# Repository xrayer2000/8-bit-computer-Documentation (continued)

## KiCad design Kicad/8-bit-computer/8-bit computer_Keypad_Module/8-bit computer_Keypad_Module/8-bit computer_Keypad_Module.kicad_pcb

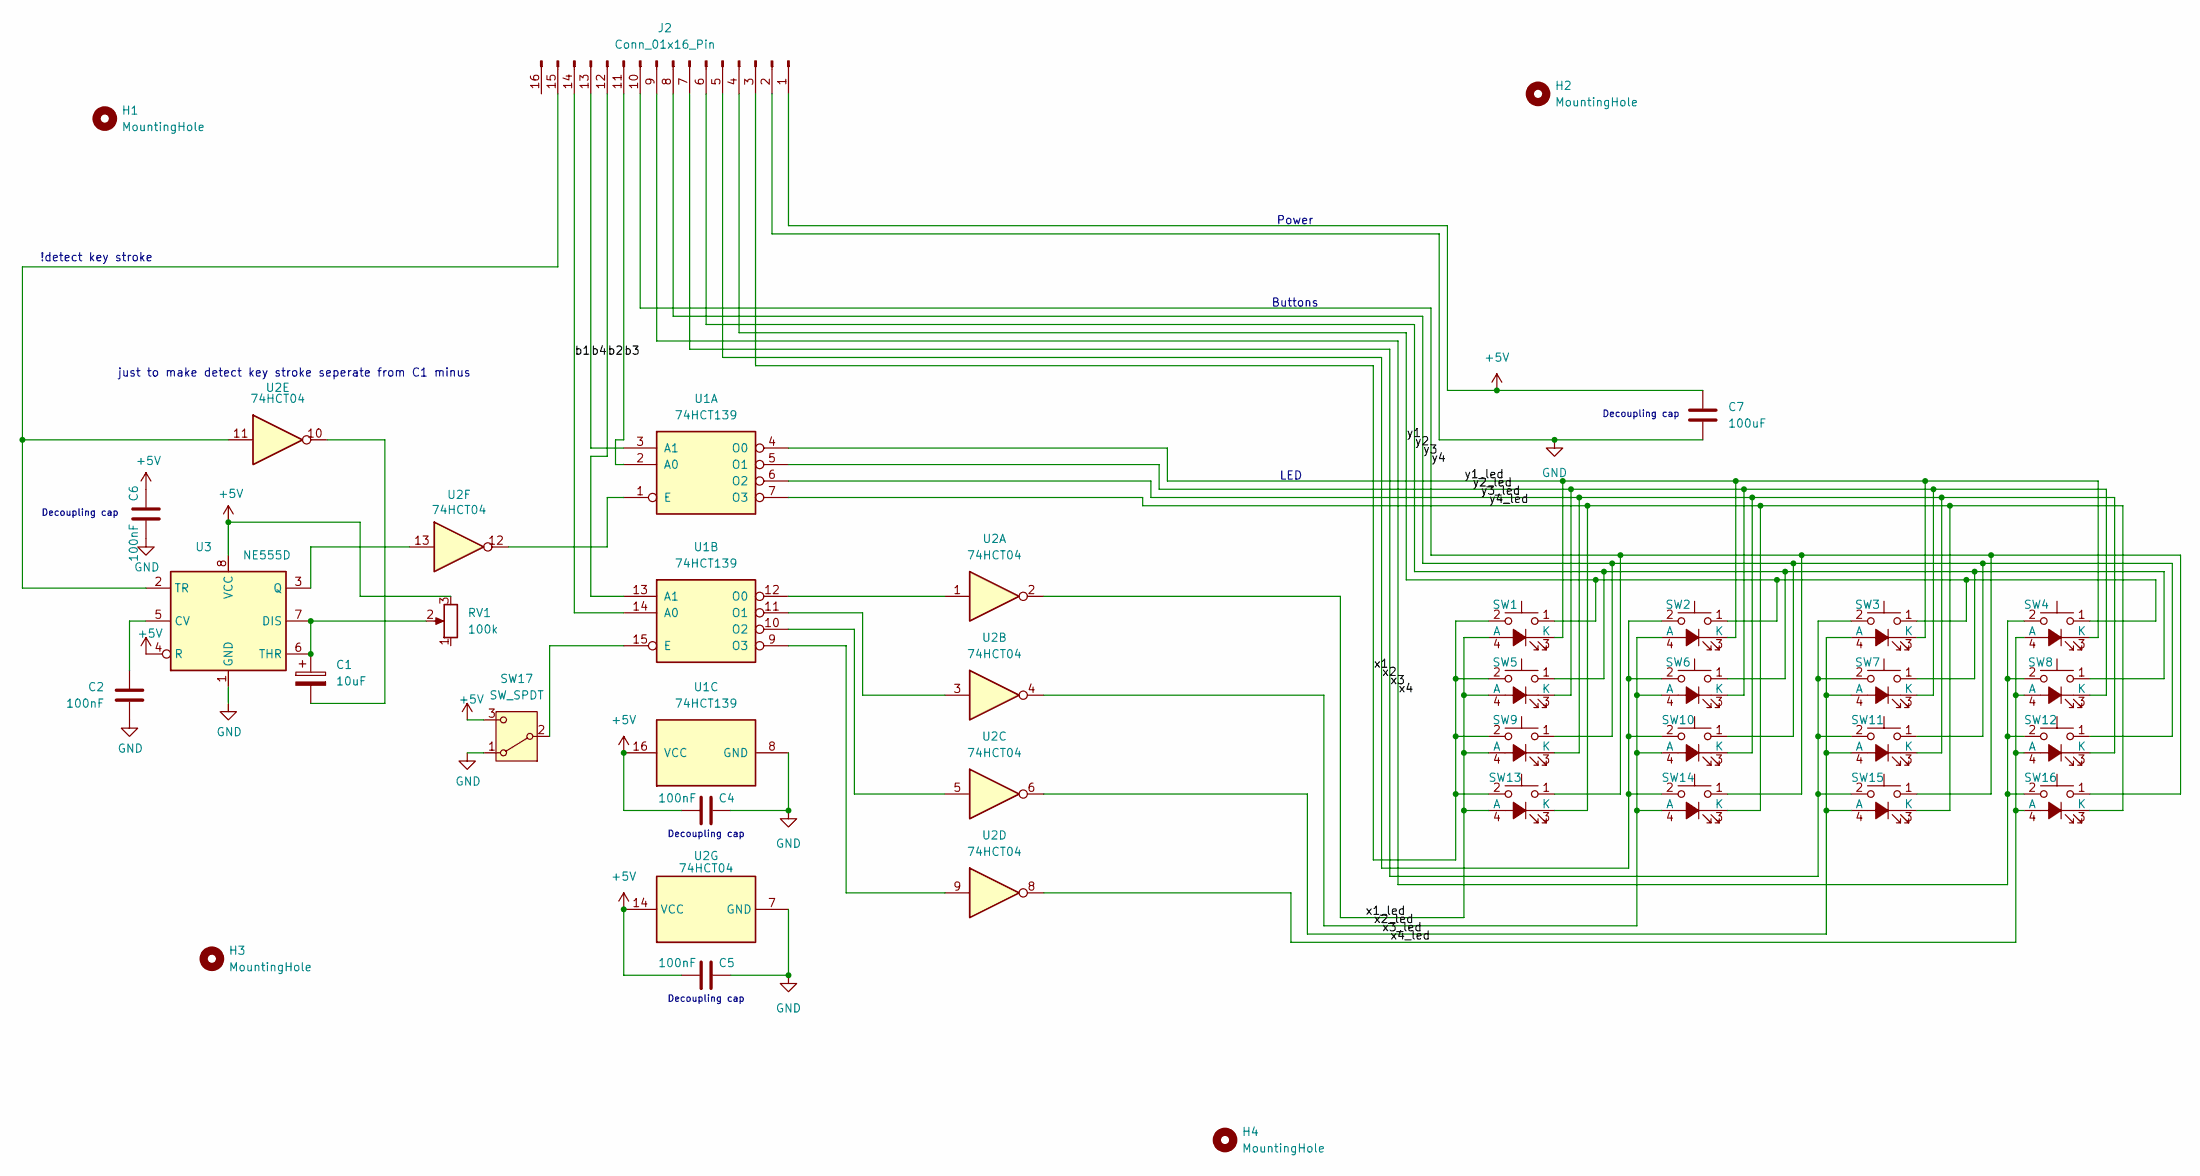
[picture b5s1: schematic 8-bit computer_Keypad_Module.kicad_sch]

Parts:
C1: 10uF; CP_Radial_D5.0mm_P2.00mm
C2: 100nF; CP_Radial_D5.0mm_P2.00mm
C4, C5, C6: 100nF; C_Disc_D3.0mm_W1.6mm_P2.50mm
C7: 100uF; CP_Radial_D4.0mm_P1.50mm
H1, H2, H3, H4: MountingHole; MountingHole_3.2mm_M3_DIN965_Pad
J2: Conn_01x16_Pin; IDC-Header_2x08_P2.54mm_Vertical
RV1: 100k; Potentiometer_Bourns_3296W_Vertical
SW1, SW2, SW3, SW4, SW5, SW6, SW7, SW8, SW9, SW10, SW11, SW12, SW13, SW14, SW15, SW16: CherryMX_LED; CherryMX_1.00u_LED
SW17: SW_SPDT; hole for bistable switch
U1: 74HCT139; DIP-16_W7.62mm
U2: 74HCT04; DIP-14_W7.62mm
U3: NE555D; DIP-8_W7.62mm

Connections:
+5V: C4.1, C5.1, C6.2, C7.2, J2.1, RV1.3, SW17.3 (C), U1.16 (VCC), U2.14 (VCC), U3.4 (R), U3.8 (VCC)
/b1: J2.14, U1.14 (A0)
/b2: J2.12, U1.13 (A1)
/b3: J2.11, U1.2 (A0)
/b4: J2.13, U1.3 (A1)
/x1: J2.3, SW1.2, SW5.2, SW9.2, SW13.2
/x1_led: SW1.4 (A), SW5.4 (A), SW9.4 (A), SW13.4 (A), U2.2
/x2: J2.5, SW2.2, SW6.2, SW10.2, SW14.2
/x2_led: SW2.4 (A), SW6.4 (A), SW10.4 (A), SW14.4 (A), U2.4
/x3: J2.7, SW3.2, SW7.2, SW11.2, SW15.2
/x3_led: SW3.4 (A), SW7.4 (A), SW11.4 (A), SW15.4 (A), U2.6
/x4: J2.9, SW4.2, SW8.2, SW12.2, SW16.2
/x4_led: SW4.4 (A), SW8.4 (A), SW12.4 (A), SW16.4 (A), U2.8
/y1: J2.4, SW1.1, SW2.1, SW3.1, SW4.1
/y1_led: SW1.3 (K), SW2.3 (K), SW3.3 (K), SW4.3 (K), U1.4 (O0)
/y2: J2.6, SW5.1, SW6.1, SW7.1, SW8.1
/y2_led: SW5.3 (K), SW6.3 (K), SW7.3 (K), SW8.3 (K), U1.5 (O1)
/y3: J2.8, SW9.1, SW10.1, SW11.1, SW12.1
/y3_led: SW9.3 (K), SW10.3 (K), SW11.3 (K), SW12.3 (K), U1.6 (O2)
/y4: J2.10, SW13.1, SW14.1, SW15.1, SW16.1
/y4_led: SW13.3 (K), SW14.3 (K), SW15.3 (K), SW16.3 (K), U1.7 (O3)
GND: C2.1, C4.2, C5.2, C6.1, C7.1, J2.2, SW17.1 (A), U1.8 (GND), U2.7 (GND), U3.1 (GND)
unnamed: C1.2, U2.10
unnamed: J2.15, U2.11, U3.2 (TR)
unnamed: SW17.2 (B), U1.15 (E)
unnamed: U1.1 (E), U2.12
unnamed: U1.12 (O0), U2.1
unnamed: U1.11 (O1), U2.3
unnamed: U1.10 (O2), U2.5
unnamed: U1.9 (O3), U2.9
unnamed: C2.2, U3.5 (CV)
unnamed: C1.1, RV1.2, U3.6 (THR), U3.7 (DIS)
unnamed: U2.13, U3.3 (Q)

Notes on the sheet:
Decoupling cap
Power
Buttons
just to make detect key stroke seperate from C1 minus
!detect key stroke
LED

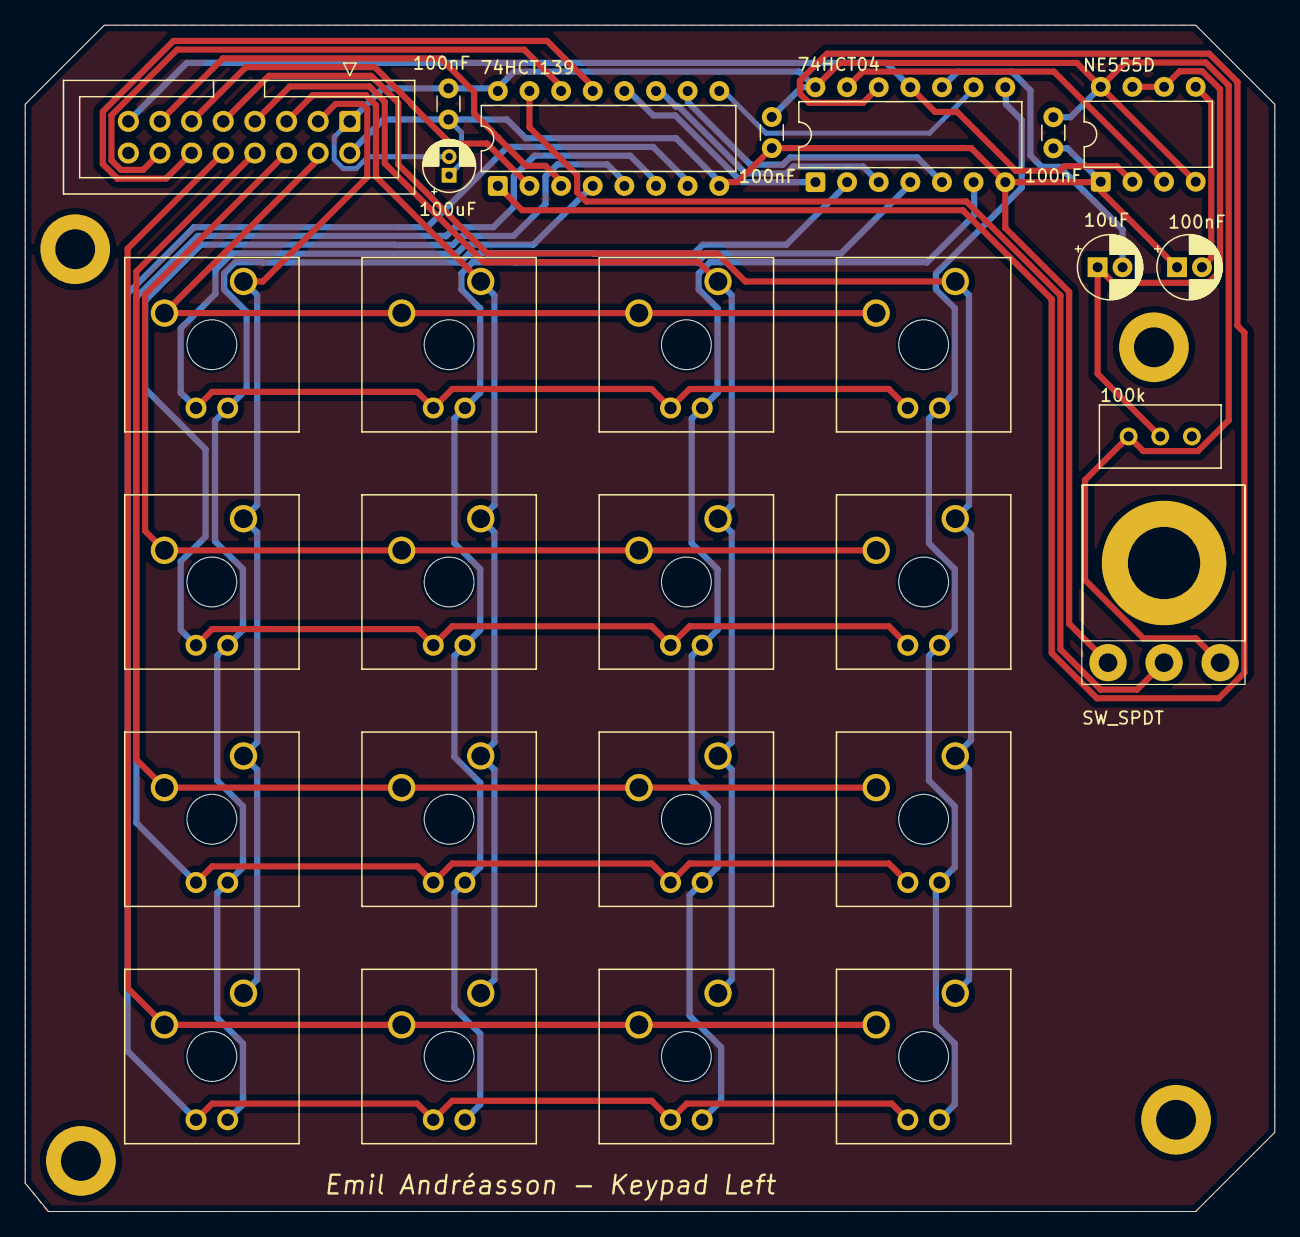
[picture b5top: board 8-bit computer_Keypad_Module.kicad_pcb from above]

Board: 2 copper layers, 100.3 x 95.2 mm, 32 parts (0 on the bottom side), 33 nets.

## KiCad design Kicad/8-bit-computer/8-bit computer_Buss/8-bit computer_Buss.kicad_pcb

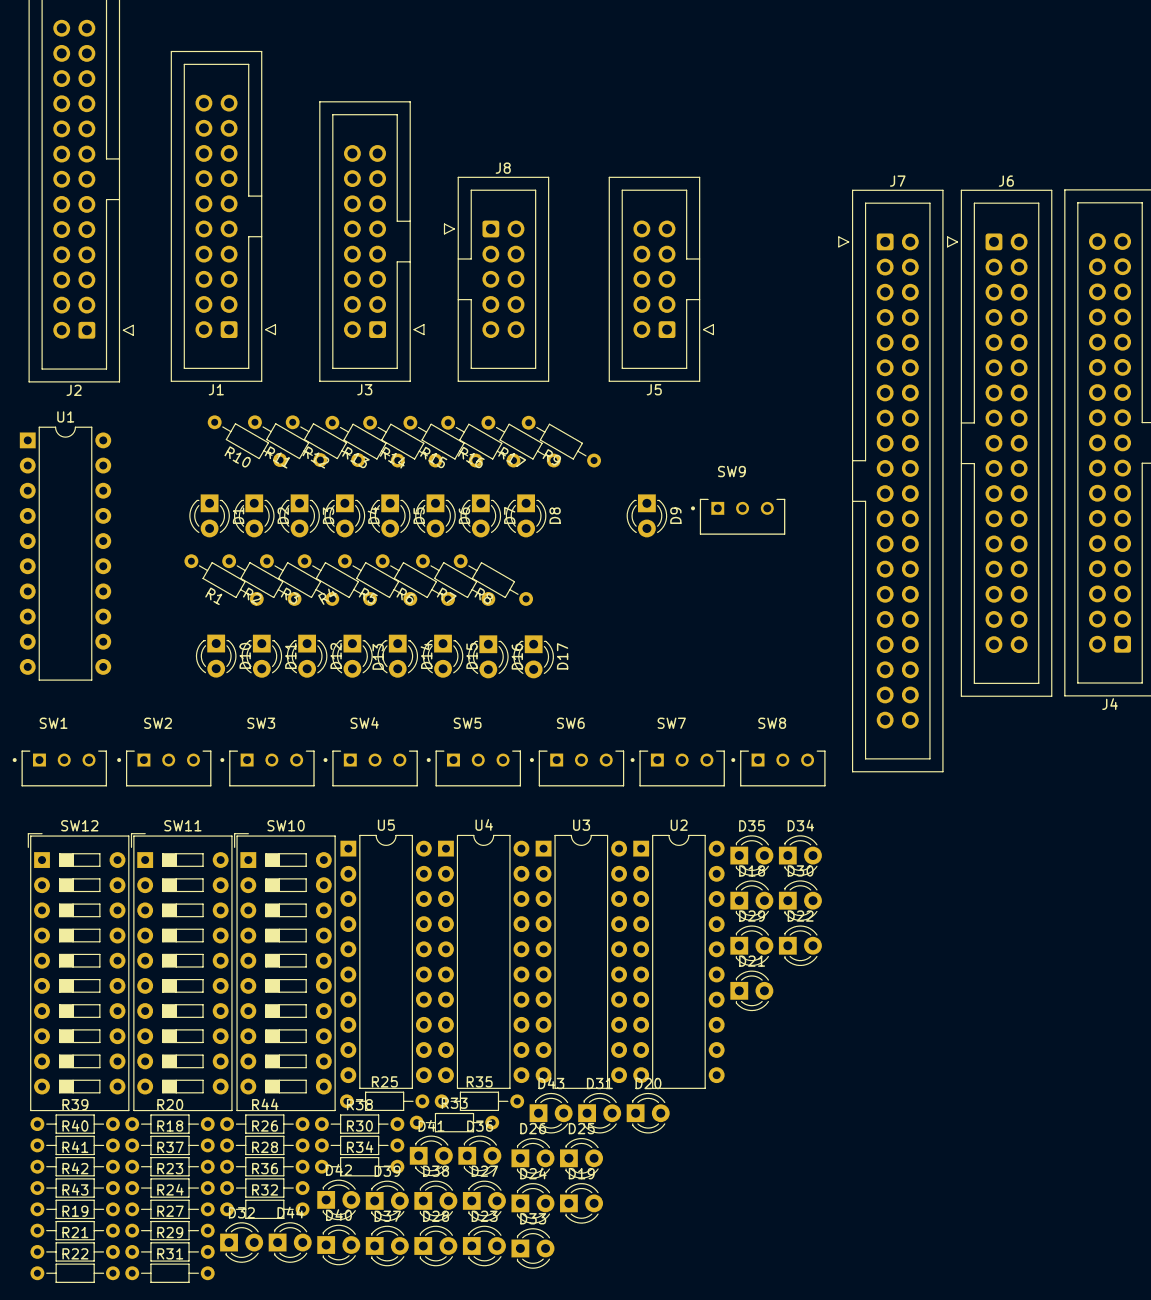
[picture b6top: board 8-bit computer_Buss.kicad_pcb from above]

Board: 2 copper layers, 113 parts (0 on the bottom side), 65 nets, no tracks yet.

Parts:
D1, D2, D3, D4, D5, D6, D7, D8, D9, D10, D11, D12, D13, D14, D15, D16, D17, D18, D19, D20, D21, D22, D23, D24, D25, D26, D27, D28, D29, D30, D31, D32, D33, D34, D35, D36, D37, D38, D39, D40, D41, D42, D43, D44: LED; LED_D3.0mm
J1: General Registers; IDC-Header_2x10_P2.54mm_Vertical
J2: ALU; IDC-Header_2x13_P2.54mm_Vertical
J3: PC and Stack pointer register; IDC-Header_2x08_P2.54mm_Vertical
J4: RAM; IDC-Header_2x17_P2.54mm_Vertical
J5: Bot Loader; IDC-Header_2x05_P2.54mm_Vertical
J6: Input module; IDC-Header_2x17_P2.54mm_Vertical
J7: Control Matrix; IDC-Header_2x20_P2.54mm_Vertical
J8: Clock; IDC-Header_2x05_P2.54mm_Vertical
R1, R2, R3, R10, R11, R12, R13, R14, R15, R16, R17, R18, R19, R20, R26, R27, R28, R34, R35, R36: 1000; R_Axial_DIN0204_L3.6mm_D1.6mm_P7.62mm_Horizontal
R4, R5, R6, R7, R8, R21, R22, R23, R24, R25, R29, R30, R31, R32, R33, R37, R38, R39, R40, R41, R42, R43, R44: R; R_Axial_DIN0204_L3.6mm_D1.6mm_P7.62mm_Horizontal
R9: 470; R_Axial_DIN0204_L3.6mm_D1.6mm_P7.62mm_Horizontal
SW1, SW2, SW3, SW4, SW5, SW6, SW7, SW8, SW9: SW_DIP_x01; SW_EG1270
SW10, SW11, SW12: SW_DIP_x10; SW_DIP_SPSTx10_Slide_9.78x27.58mm_W7.62mm_P2.54mm
U1, U2, U3, U4, U5: 74LS245; DIP-20_W7.62mm

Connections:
+5V: D9.2, SW1.1, SW2.1, SW3.1, SW4.1, SW5.1, SW6.1, SW7.1, SW8.1, U1.1
GND: R1.2, R2.2, R3.2, R4.2, R5.2, R6.2, R7.2, R8.2, R10.2, R11.2, R12.2, R13.2, R14.2, R15.2, R16.2, R17.2, SW9.1, U1.10
unnamed: D1.1, R10.1
unnamed: D2.1, R11.1
unnamed: D3.1, R12.1
unnamed: D4.1, R13.1
unnamed: D5.1, R14.1
unnamed: D6.1, R15.1
unnamed: D7.1, R16.1
unnamed: D8.1, R17.1
unnamed: D9.1, R9.1
unnamed: D10.1, R1.1
unnamed: D10.2, SW4.2, U1.2
unnamed: D11.1, R2.1
unnamed: D11.2, SW5.2, U1.3
unnamed: D12.1, R3.1
unnamed: D12.2, SW6.2, U1.4
unnamed: D13.1, R4.1
unnamed: D13.2, SW7.2, U1.5
unnamed: D14.1, R5.1
unnamed: D14.2, SW8.2, U1.6
unnamed: D15.1, R6.1
unnamed: D15.2, SW1.2, U1.7
unnamed: D16.1, R7.1
unnamed: D16.2, SW2.2, U1.8
unnamed: D17.1, R8.1
unnamed: D17.2, SW3.2, U1.9
unnamed: D18.1, R18.1
unnamed: D19.1, R19.1
unnamed: D20.1, R20.1
unnamed: D21.1, R21.1
unnamed: D22.1, R22.1
unnamed: D23.1, R23.1
unnamed: D24.1, R24.1
unnamed: D25.1, R25.1
unnamed: D26.1, R26.1
unnamed: D27.1, R27.1
unnamed: D28.1, R28.1
unnamed: D29.1, R29.1
unnamed: D30.1, R30.1
unnamed: D31.1, R31.1
unnamed: D32.1, R32.1
unnamed: D33.1, R33.1
unnamed: D34.1, R34.1
unnamed: D35.1, R35.1
unnamed: D36.1, R36.1
unnamed: D37.1, R37.1
unnamed: D38.1, R38.1
unnamed: D39.1, R39.1
unnamed: D40.1, R40.1
unnamed: D41.1, R41.1
unnamed: D42.1, R42.1
unnamed: D43.1, R43.1
unnamed: D44.1, R44.1
unnamed: J1.1, J2.1, J3.1, U1.18
unnamed: J1.2, J2.2, J3.2, U1.17
unnamed: J1.3, J2.3, J3.3, U1.16
unnamed: J1.4, J2.4, J3.4, U1.15
unnamed: J1.5, J2.5, J3.5, U1.14
unnamed: J1.6, J2.6, J3.6, U1.13
unnamed: J1.7, J2.7, U1.12
unnamed: J1.8, J2.8, U1.11
unnamed: R9.2, SW9.2, U1.19
unnamed: R18.2, R19.2, R20.2, R21.2, R22.2, R23.2, R24.2, R25.2, R26.2, R27.2, R28.2, R29.2, R30.2, R31.2, R32.2, R33.2, R34.2, R35.2, R36.2, R37.2, R38.2, R39.2, R40.2, R41.2, R42.2, R43.2, R44.2
unnamed: SW10.1, SW10.2, SW10.3, SW10.4, SW10.5, SW10.6, SW10.7, SW10.8, SW10.9, SW10.10, SW11.1, SW11.2, SW11.3, SW11.4, SW11.5, SW11.6, SW11.7, SW11.8, SW11.9, SW11.10, SW12.1, SW12.2, SW12.3, SW12.4, SW12.5, SW12.6, SW12.7, SW12.8, SW12.9, SW12.10

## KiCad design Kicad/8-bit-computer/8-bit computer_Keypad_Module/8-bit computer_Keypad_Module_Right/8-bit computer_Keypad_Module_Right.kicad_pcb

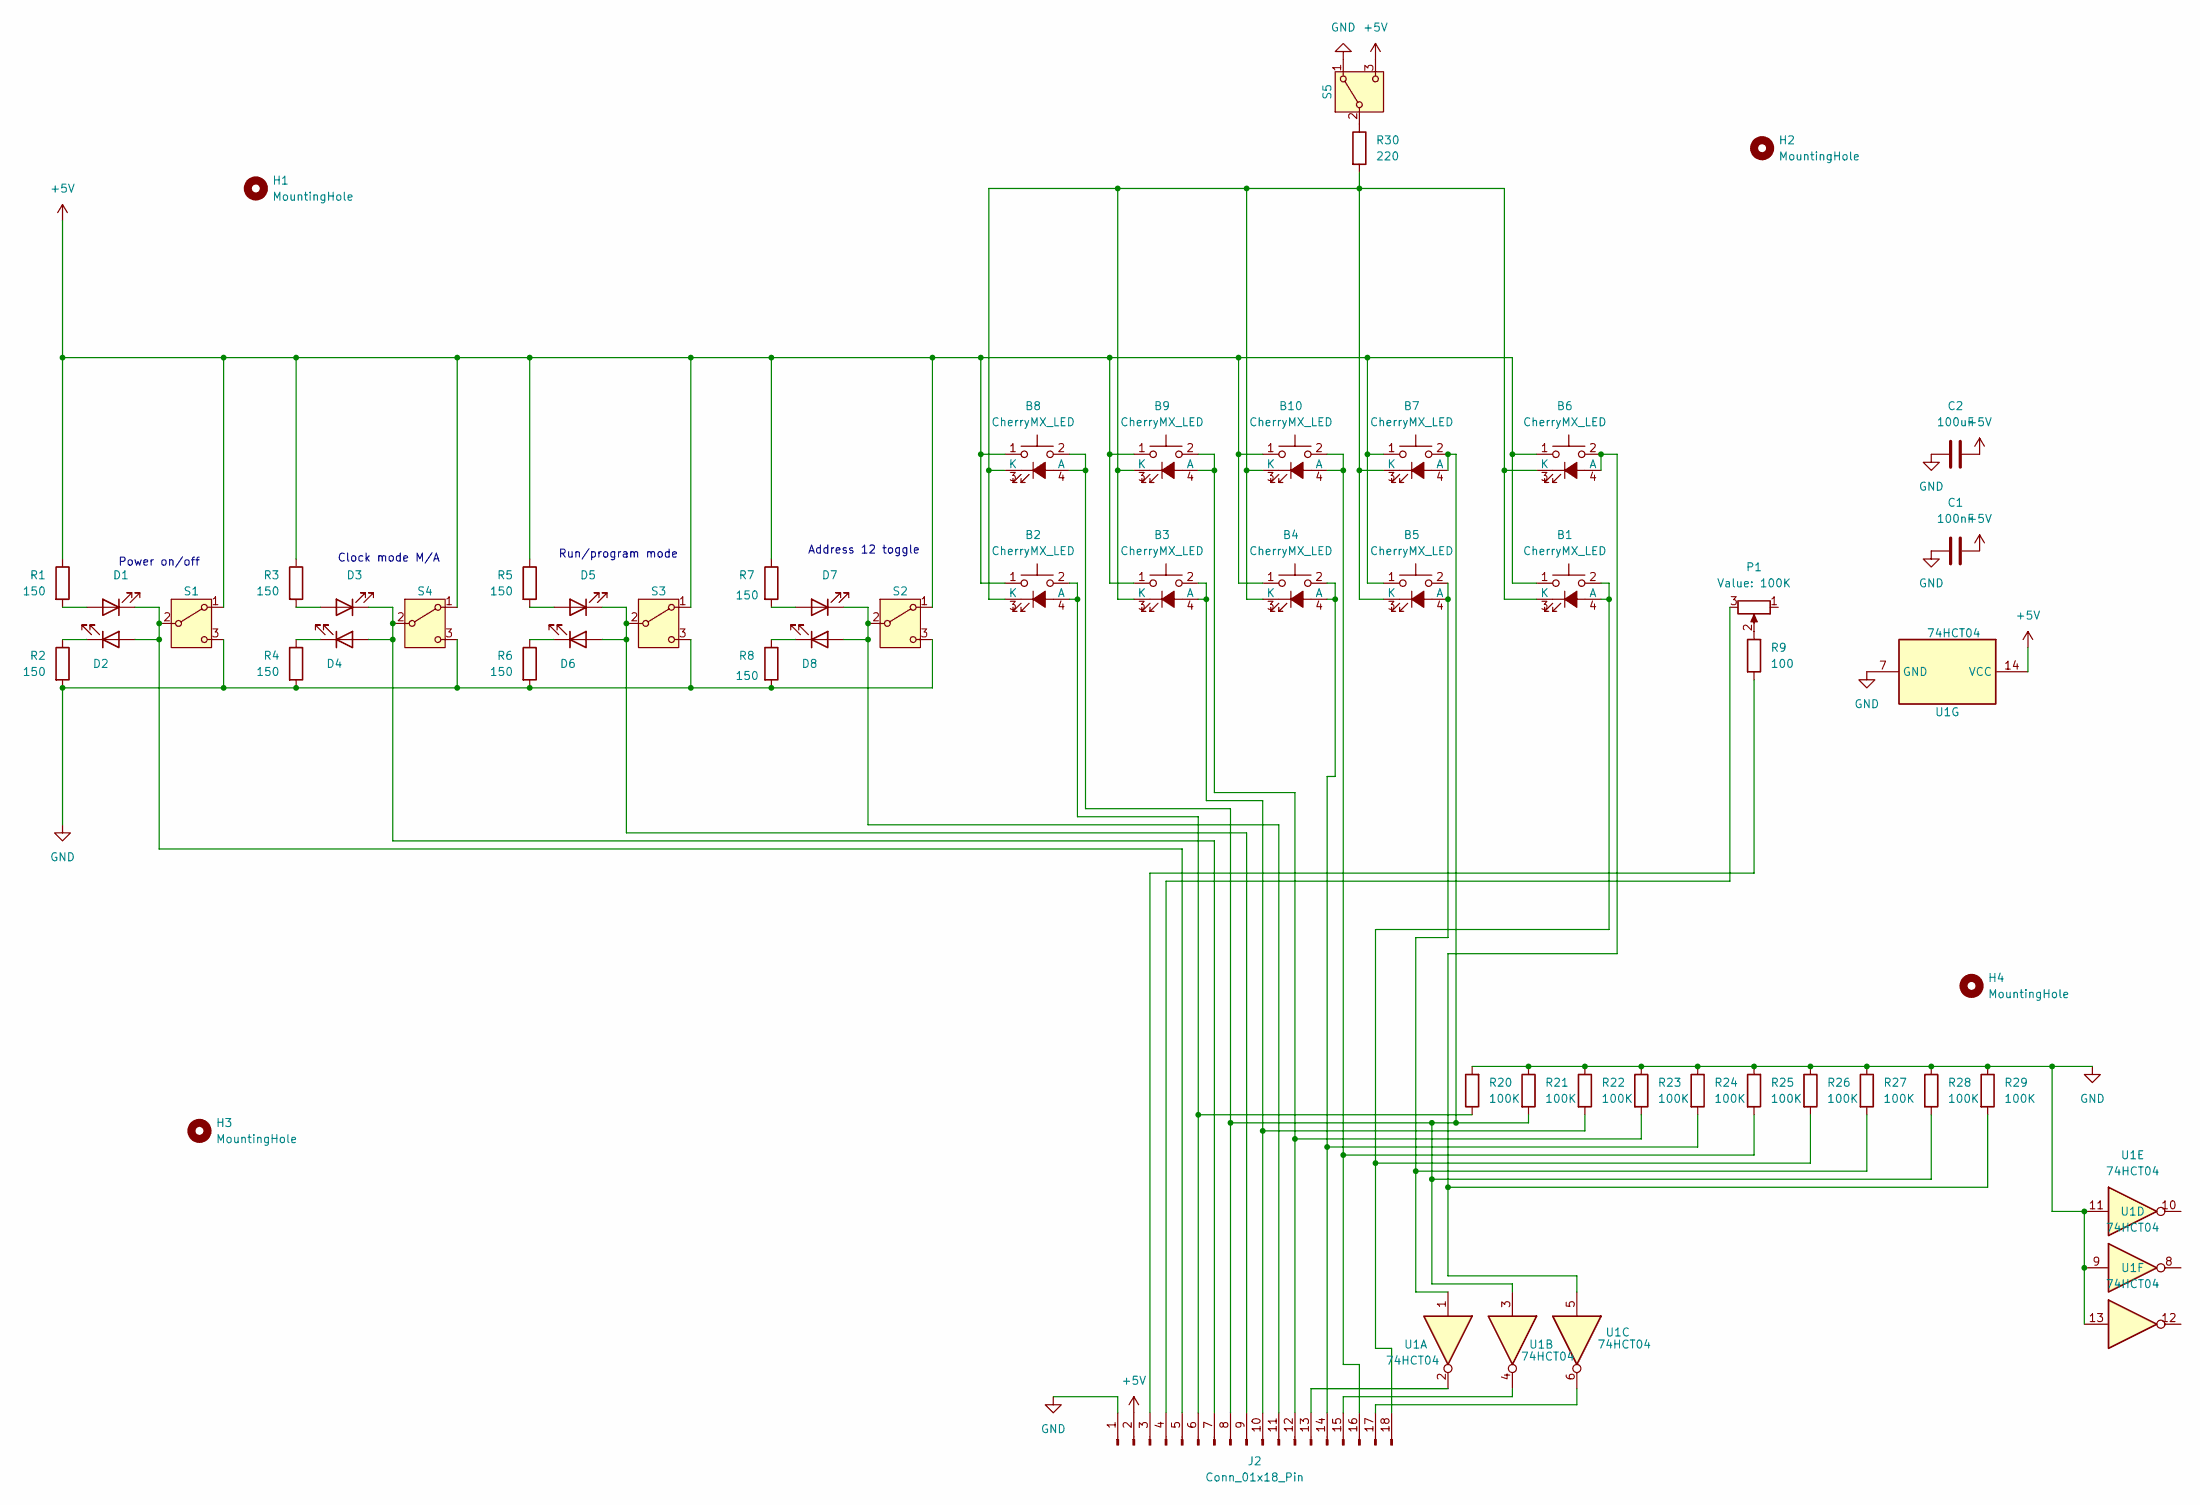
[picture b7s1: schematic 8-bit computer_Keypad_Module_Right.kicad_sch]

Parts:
B1, B2, B3, B4, B5, B6, B7, B8, B9, B10: CherryMX_LED; CherryMX_1.00u_LED
C1: 100nF; C_Disc_D3.0mm_W1.6mm_P2.50mm
C2: 100uF; CP_Radial_D4.0mm_P2.00mm
D1, D2, D3, D4, D5, D6, D7, D8: LED; LED_D3.0mm
H1, H2, H3, H4: MountingHole; MountingHole_3.2mm_M3_DIN965_Pad
J2: Conn_01x18_Pin; IDC-Header_2x09_P2.54mm_Vertical
P1: 100K; hole for potentiometer
R1, R2, R3, R4, R5, R6, R7, R8: 150; R_Axial_DIN0207_L6.3mm_D2.5mm_P10.16mm_Horizontal
R9: 100; R_Axial_DIN0207_L6.3mm_D2.5mm_P10.16mm_Horizontal
R20, R21, R22, R23, R24, R25, R26, R27, R28, R29: 100K; R_Axial_DIN0207_L6.3mm_D2.5mm_P10.16mm_Horizontal
R30: 220; R_Axial_DIN0207_L6.3mm_D2.5mm_P10.16mm_Horizontal
S1, S2, S3, S4, S5: SW_SPDT; hole for bistable switch
U1: 74HCT04; DIP-14_W7.62mm

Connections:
+5V: B1.1, B2.1, B3.1, B4.1, B5.1, B6.1, B7.1, B8.1, B9.1, B10.1, C1.1, C2.1, J2.2, R1.1, R3.1, R5.1, R7.1, S1.1 (A), S2.1 (A), S3.1 (A), S4.1 (A), S5.3 (C), U1.14 (VCC)
GND: C1.2, C2.2, J2.1, R2.2, R4.2, R6.2, R8.2, R20.2, R21.1, R22.1, R23.1, R24.1, R25.1, R26.1, R27.1, R28.1, R29.1, S1.3 (C), S2.3 (C), S3.3 (C), S4.3 (C), S5.1 (A), U1.7 (GND), U1.9, U1.11, U1.13
unnamed: B1.2, B1.4 (A), J2.18, R26.2
unnamed: B1.3 (K), B2.3 (K), B3.3 (K), B4.3 (K), B5.3 (K), B6.3 (K), B7.3 (K), B8.3 (K), B9.3 (K), B10.3 (K), R30.2
unnamed: B2.2, B2.4 (A), J2.6, R20.1
unnamed: B3.2, B3.4 (A), J2.10, R22.2
unnamed: B4.2, B4.4 (A), J2.14, R24.2
unnamed: B5.2, B5.4 (A), R27.2, U1.1
unnamed: B6.2, B6.4 (A), R29.2, U1.5
unnamed: B7.2, B7.4 (A), B8.2, B8.4 (A), J2.8, R21.2, R28.2, U1.3
unnamed: B9.2, B9.4 (A), J2.12, R23.2
unnamed: B10.2, B10.4 (A), J2.16, R25.2
unnamed: D1.2 (A), R1.2
unnamed: D1.1 (K), D2.2 (A), J2.5, S1.2 (B)
unnamed: D2.1 (K), R2.1
unnamed: D3.2 (A), R3.2
unnamed: D3.1 (K), D4.2 (A), J2.7, S4.2 (B)
unnamed: D4.1 (K), R4.1
unnamed: D5.2 (A), R5.2
unnamed: D5.1 (K), D6.2 (A), J2.9, S3.2 (B)
unnamed: D6.1 (K), R6.1
unnamed: D7.2 (A), R7.2
unnamed: D7.1 (K), D8.2 (A), J2.11, S2.2 (B)
unnamed: D8.1 (K), R8.1
unnamed: J2.3, R9.2
unnamed: J2.4, P1.3
unnamed: J2.13, U1.2
unnamed: J2.15, U1.4
unnamed: J2.17, U1.6
unnamed: P1.2, R9.1
unnamed: R30.1, S5.2 (B)

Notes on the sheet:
Run/program mode
Power on/off
Address 12 toggle
Clock mode M/A

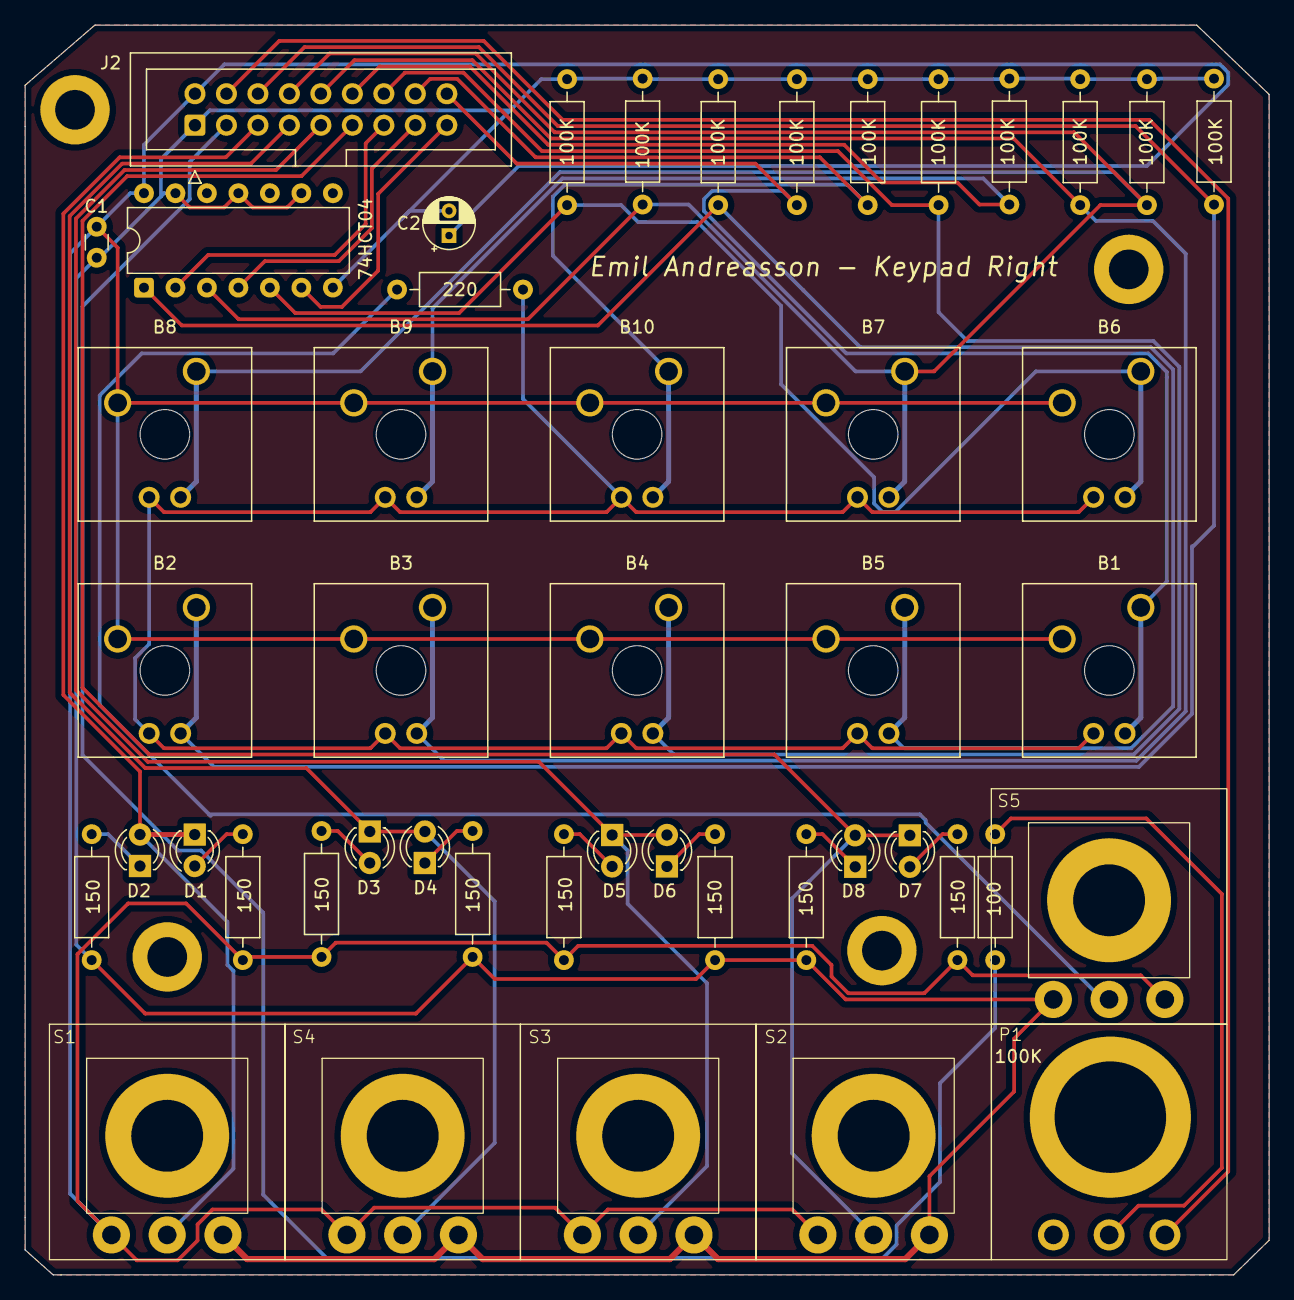
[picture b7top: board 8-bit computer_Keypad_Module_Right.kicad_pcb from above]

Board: 2 copper layers, 100.4 x 100.8 mm, 52 parts (0 on the bottom side), 31 nets.

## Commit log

2025-06-16 added gitignore
2025-06-16 added falstad map
2025-06-16 Create LICENCE
2025-06-17 modified gitignore
2025-06-17 added 8-bit computer.pdf
2025-06-17 modifed gitignore
2025-06-17 added all module schematics
2025-06-17 added Arduino Code
2025-06-17 added IO 8-bit computer
2025-06-17 added picture
2025-06-17 added kicad
